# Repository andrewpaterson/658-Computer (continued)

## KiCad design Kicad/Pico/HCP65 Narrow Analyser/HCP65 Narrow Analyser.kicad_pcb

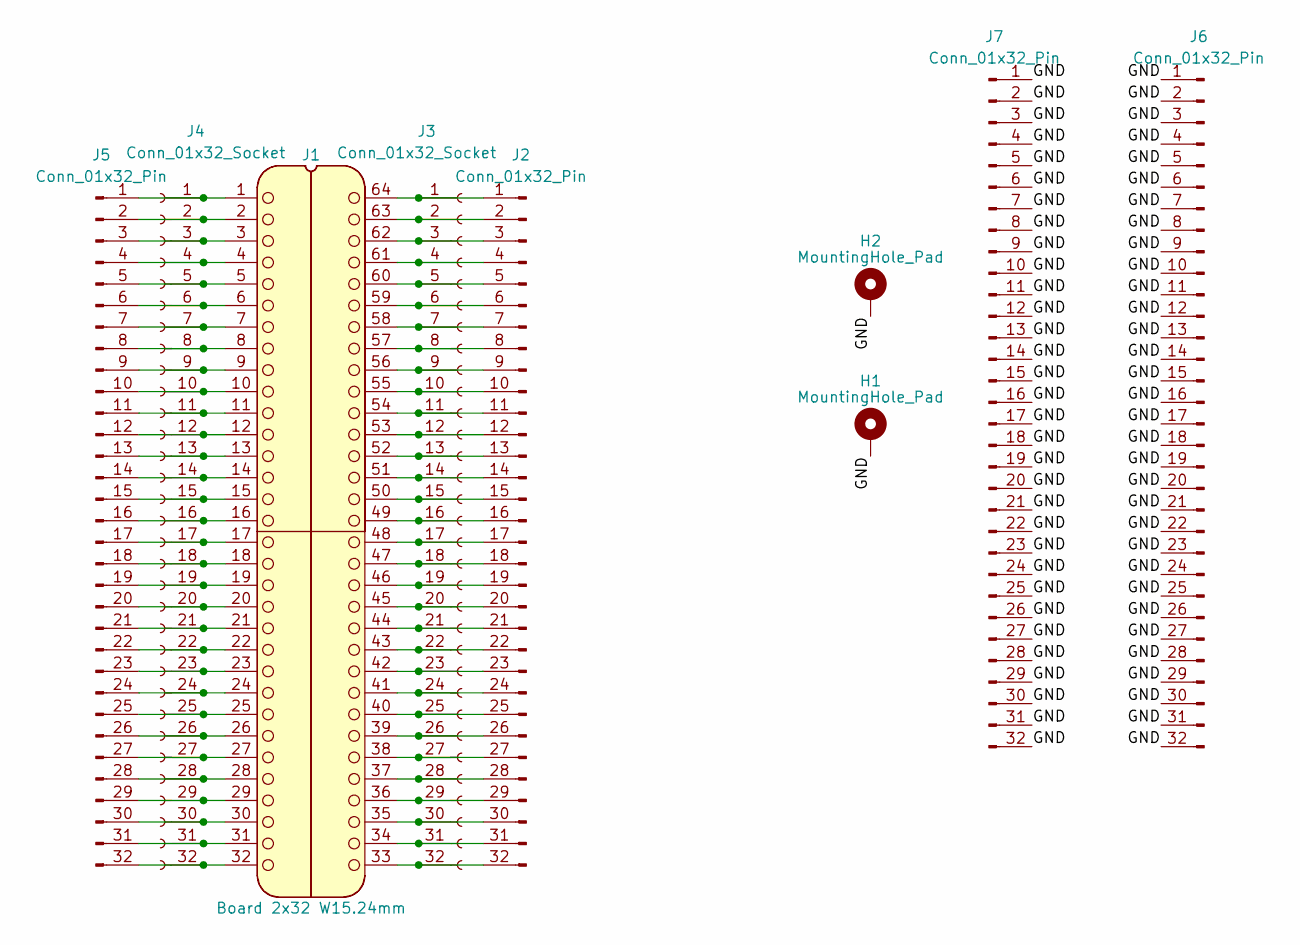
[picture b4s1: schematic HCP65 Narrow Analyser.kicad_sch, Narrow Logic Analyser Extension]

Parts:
H1, H2: MountingHole_Pad; MountingHole_3.2mm_M3_Pad
J1: Board 2x32 W15.24mm; DIP-64_Board_W15.24mm_Nak
J2, J5, J6, J7: Conn_01x32_Pin; PinHeader_1x32_P2.54mm_Vertical
J3, J4: Conn_01x32_Socket; PinSocket_1x32_P2.54mm_Vertical

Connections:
/GND: H1.1, H2.1, J6.1, J6.2, J6.3, J6.4, J6.5, J6.6, J6.7, J6.8, J6.9, J6.10, J6.11, J6.12, J6.13, J6.14, J6.15, J6.16, J6.17, J6.18, J6.19, J6.20, J6.21, J6.22, J6.23, J6.24, J6.25, J6.26, J6.27, J6.28, J6.29, J6.30, J6.31, J6.32, J7.1, J7.2, J7.3, J7.4, J7.5, J7.6, J7.7, J7.8, J7.9, J7.10, J7.11, J7.12, J7.13, J7.14, J7.15, J7.16, J7.17, J7.18, J7.19, J7.20, J7.21, J7.22, J7.23, J7.24, J7.25, J7.26, J7.27, J7.28, J7.29, J7.30, J7.31, J7.32
unnamed: J1.64, J2.1, J3.1
unnamed: J1.63, J2.2, J3.2
unnamed: J1.62, J2.3, J3.3
unnamed: J1.61, J2.4, J3.4
unnamed: J1.60, J2.5, J3.5
unnamed: J1.59, J2.6, J3.6
unnamed: J1.58, J2.7, J3.7
unnamed: J1.57, J2.8, J3.8
unnamed: J1.56, J2.9, J3.9
unnamed: J1.55, J2.10, J3.10
unnamed: J1.54, J2.11, J3.11
unnamed: J1.53, J2.12, J3.12
unnamed: J1.52, J2.13, J3.13
unnamed: J1.51, J2.14, J3.14
unnamed: J1.50, J2.15, J3.15
unnamed: J1.49, J2.16, J3.16
unnamed: J1.48, J2.17, J3.17
unnamed: J1.47, J2.18, J3.18
unnamed: J1.46, J2.19, J3.19
unnamed: J1.45, J2.20, J3.20
unnamed: J1.44, J2.21, J3.21
unnamed: J1.43, J2.22, J3.22
unnamed: J1.42, J2.23, J3.23
unnamed: J1.41, J2.24, J3.24
unnamed: J1.40, J2.25, J3.25
unnamed: J1.39, J2.26, J3.26
unnamed: J1.38, J2.27, J3.27
unnamed: J1.37, J2.28, J3.28
unnamed: J1.36, J2.29, J3.29
unnamed: J1.35, J2.30, J3.30
unnamed: J1.34, J2.31, J3.31
unnamed: J1.33, J2.32, J3.32
unnamed: J1.1, J4.1, J5.1
unnamed: J1.2, J4.2, J5.2
unnamed: J1.3, J4.3, J5.3
unnamed: J1.4, J4.4, J5.4
unnamed: J1.5, J4.5, J5.5
unnamed: J1.6, J4.6, J5.6
unnamed: J1.7, J4.7, J5.7
unnamed: J1.8, J4.8, J5.8
unnamed: J1.9, J4.9, J5.9
unnamed: J1.10, J4.10, J5.10
unnamed: J1.11, J4.11, J5.11
unnamed: J1.12, J4.12, J5.12
unnamed: J1.13, J4.13, J5.13
unnamed: J1.14, J4.14, J5.14
unnamed: J1.15, J4.15, J5.15
unnamed: J1.16, J4.16, J5.16
unnamed: J1.17, J4.17, J5.17
unnamed: J1.18, J4.18, J5.18
unnamed: J1.19, J4.19, J5.19
unnamed: J1.20, J4.20, J5.20
unnamed: J1.21, J4.21, J5.21
unnamed: J1.22, J4.22, J5.22
unnamed: J1.23, J4.23, J5.23
unnamed: J1.24, J4.24, J5.24
unnamed: J1.25, J4.25, J5.25
unnamed: J1.26, J4.26, J5.26
unnamed: J1.27, J4.27, J5.27
unnamed: J1.28, J4.28, J5.28
unnamed: J1.29, J4.29, J5.29
unnamed: J1.30, J4.30, J5.30
unnamed: J1.31, J4.31, J5.31
unnamed: J1.32, J4.32, J5.32

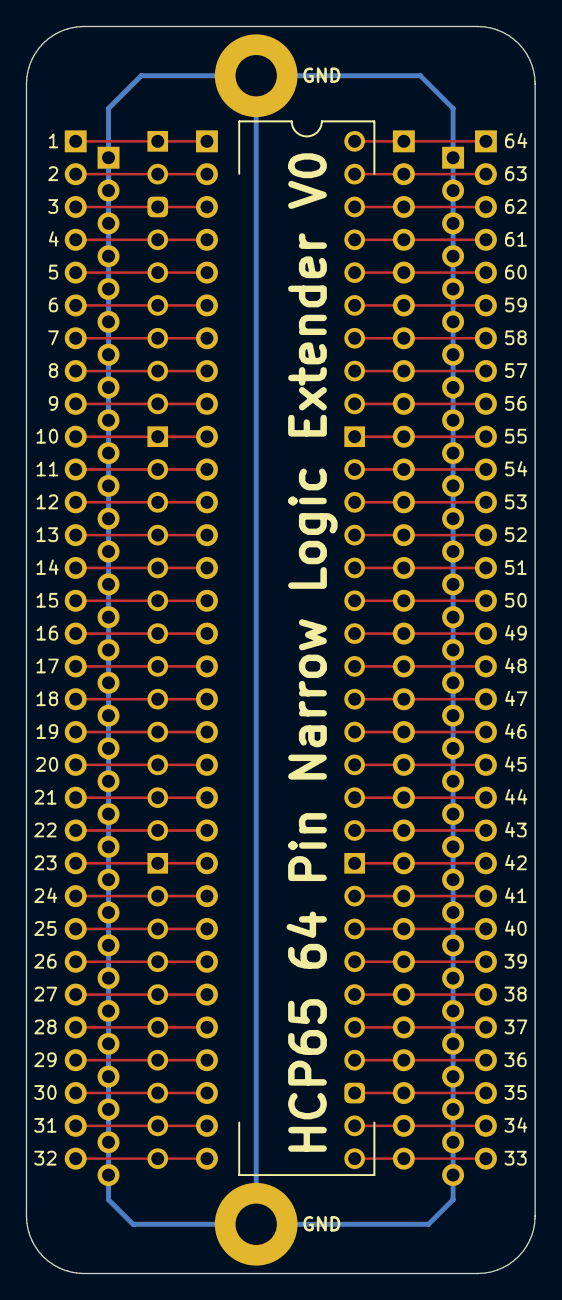
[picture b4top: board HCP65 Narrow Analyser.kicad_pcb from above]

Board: 2 copper layers, 39.4 x 96.5 mm, 9 parts (0 on the bottom side), 65 nets.

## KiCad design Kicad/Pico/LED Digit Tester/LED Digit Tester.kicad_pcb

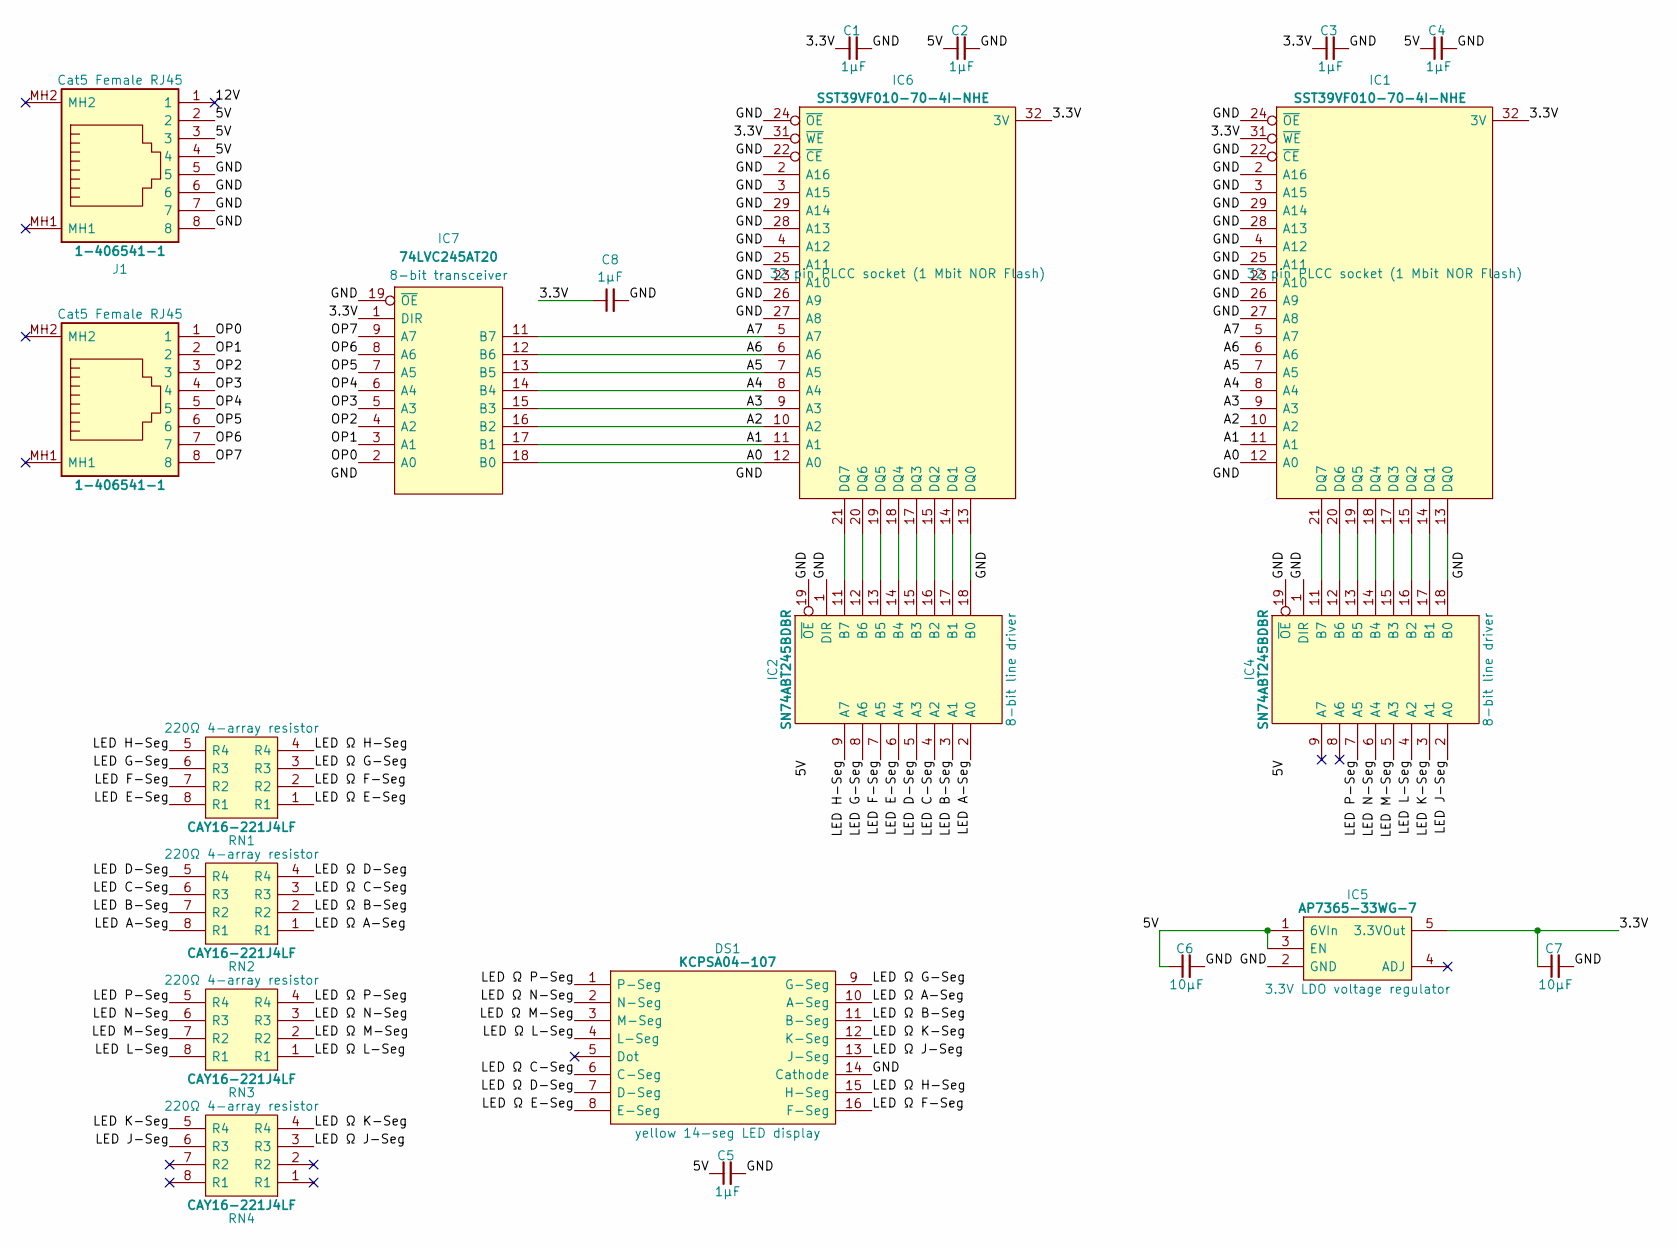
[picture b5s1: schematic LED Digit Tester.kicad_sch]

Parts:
C1, C2, C3, C4, C5, C8: 1μF; C_0805
C6, C7: 10µF; C_0805
DS1: KCPSA04-107; KCPSA04107; Manufacturer_Part_Number KCPSA04-107; Mouser Part Number N/A
IC1, IC6: SST39VF010-70-4I-NHE; 5408803224008; Manufacturer_Part_Number SST39VF010-70-4I-NHE
IC2, IC4: SN74ABT245BDBR; SOP65P780X200-20N; Manufacturer_Part_Number SN74ABT245BDBR; Mouser Part Number 595-SN74ABT245BDBR
IC5: AP7365-33WG-7; SOT95P285X130-5N; Manufacturer_Part_Number AP7365-33WG-7; Mouser Part Number 621-AP7365-33WG-7
IC7: 74LVC245AT20; SOP65P640X120-20N; Manufacturer_Part_Number 74LVC245AT20-13; Mouser Part Number 621-74LVC245AT20-13
J1, J2: 1-406541-1; 1-406541-1_1; Manufacturer_Part_Number 1-406541-1; Mouser Part Number 571-1-406541-1
RN1, RN2, RN3, RN4: CAY16-221J4LF; CAY16-F4; Manufacturer_Part_Number CAY16-221J4LF; Mouser Part Number 652-CAY16-221J4LF

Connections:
/3.3V: C1.1, C3.1, C7.1, C8.1, IC1.31 (~WE), IC1.32 (3V), IC5.5 (3.3VOut), IC6.31 (~WE), IC6.32 (3V), IC7.1 (DIR), IC7.20 (3V)
/5V: C2.1, C4.1, C5.1, C6.1, IC2.20 (5V), IC4.20 (5V), IC5.1 (6VIn), IC5.3 (EN), J1.2, J1.3, J1.4
/12V: J1.1
/A0: IC1.12 (A0), IC6.12 (A0), IC7.18 (B0)
/A1: IC1.11 (A1), IC6.11 (A1), IC7.17 (B1)
/A2: IC1.10 (A2), IC6.10 (A2), IC7.16 (B2)
/A3: IC1.9 (A3), IC6.9 (A3), IC7.15 (B3)
/A4: IC1.8 (A4), IC6.8 (A4), IC7.14 (B4)
/A5: IC1.7 (A5), IC6.7 (A5), IC7.13 (B5)
/A6: IC1.6 (A6), IC6.6 (A6), IC7.12 (B6)
/A7: IC1.5 (A7), IC6.5 (A7), IC7.11 (B7)
/GND: C1.2, C2.2, C3.2, C4.2, C5.2, C6.2, C7.2, C8.2, DS1.14 (Cathode), IC1.2 (A16), IC1.3 (A15), IC1.4 (A12), IC1.16 (GND), IC1.22 (~CE), IC1.23 (A10), IC1.24 (~OE), IC1.25 (A11), IC1.26 (A9), IC1.27 (A8), IC1.28 (A13), IC1.29 (A14), IC2.1 (DIR), IC2.10 (GND), IC2.19 (~OE), IC4.1 (DIR), IC4.10 (GND), IC4.19 (~OE), IC5.2 (GND), IC6.2 (A16), IC6.3 (A15), IC6.4 (A12), IC6.16 (GND), IC6.22 (~CE), IC6.23 (A10), IC6.24 (~OE), IC6.25 (A11), IC6.26 (A9), IC6.27 (A8), IC6.28 (A13), IC6.29 (A14), IC7.10 (GND), IC7.19 (~OE), J1.5, J1.6, J1.7, J1.8
/LED A-Seg: IC2.2 (A0), RN2.8 (R1)
/LED B-Seg: IC2.3 (A1), RN2.7 (R2)
/LED C-Seg: IC2.4 (A2), RN2.6 (R3)
/LED D-Seg: IC2.5 (A3), RN2.5 (R4)
/LED E-Seg: IC2.6 (A4), RN1.8 (R1)
/LED F-Seg: IC2.7 (A5), RN1.7 (R2)
/LED G-Seg: IC2.8 (A6), RN1.6 (R3)
/LED H-Seg: IC2.9 (A7), RN1.5 (R4)
/LED J-Seg: IC4.2 (A0), RN4.6 (R3)
/LED K-Seg: IC4.3 (A1), RN4.5 (R4)
/LED L-Seg: IC4.4 (A2), RN3.8 (R1)
/LED M-Seg: IC4.5 (A3), RN3.7 (R2)
/LED N-Seg: IC4.6 (A4), RN3.6 (R3)
/LED P-Seg: IC4.7 (A5), RN3.5 (R4)
/LED Ω A-Seg: DS1.10 (A-Seg), RN2.1 (R1)
/LED Ω B-Seg: DS1.11 (B-Seg), RN2.2 (R2)
/LED Ω C-Seg: DS1.6 (C-Seg), RN2.3 (R3)
/LED Ω D-Seg: DS1.7 (D-Seg), RN2.4 (R4)
/LED Ω E-Seg: DS1.8 (E-Seg), RN1.1 (R1)
/LED Ω F-Seg: DS1.16 (F-Seg), RN1.2 (R2)
/LED Ω G-Seg: DS1.9 (G-Seg), RN1.3 (R3)
/LED Ω H-Seg: DS1.15 (H-Seg), RN1.4 (R4)
/LED Ω J-Seg: DS1.13 (J-Seg), RN4.3 (R3)
/LED Ω K-Seg: DS1.12 (K-Seg), RN4.4 (R4)
/LED Ω L-Seg: DS1.4 (L-Seg), RN3.1 (R1)
/LED Ω M-Seg: DS1.3 (M-Seg), RN3.2 (R2)
/LED Ω N-Seg: DS1.2 (N-Seg), RN3.3 (R3)
/LED Ω P-Seg: DS1.1 (P-Seg), RN3.4 (R4)
/OP0: IC7.2 (A0), J2.1
/OP1: IC7.3 (A1), J2.2
/OP2: IC7.4 (A2), J2.3
/OP3: IC7.5 (A3), J2.4
/OP4: IC7.6 (A4), J2.5
/OP5: IC7.7 (A5), J2.6
/OP6: IC7.8 (A6), J2.7
/OP7: IC7.9 (A7), J2.8
unnamed: IC1.13 (DQ0), IC4.18 (B0)
unnamed: IC1.14 (DQ1), IC4.17 (B1)
unnamed: IC1.15 (DQ2), IC4.16 (B2)
unnamed: IC1.17 (DQ3), IC4.15 (B3)
unnamed: IC1.18 (DQ4), IC4.14 (B4)
unnamed: IC1.19 (DQ5), IC4.13 (B5)
unnamed: IC1.20 (DQ6), IC4.12 (B6)
unnamed: IC1.21 (DQ7), IC4.11 (B7)
unnamed: IC2.18 (B0), IC6.13 (DQ0)
unnamed: IC2.17 (B1), IC6.14 (DQ1)
unnamed: IC2.16 (B2), IC6.15 (DQ2)
unnamed: IC2.15 (B3), IC6.17 (DQ3)
unnamed: IC2.14 (B4), IC6.18 (DQ4)
unnamed: IC2.13 (B5), IC6.19 (DQ5)
unnamed: IC2.12 (B6), IC6.20 (DQ6)
unnamed: IC2.11 (B7), IC6.21 (DQ7)

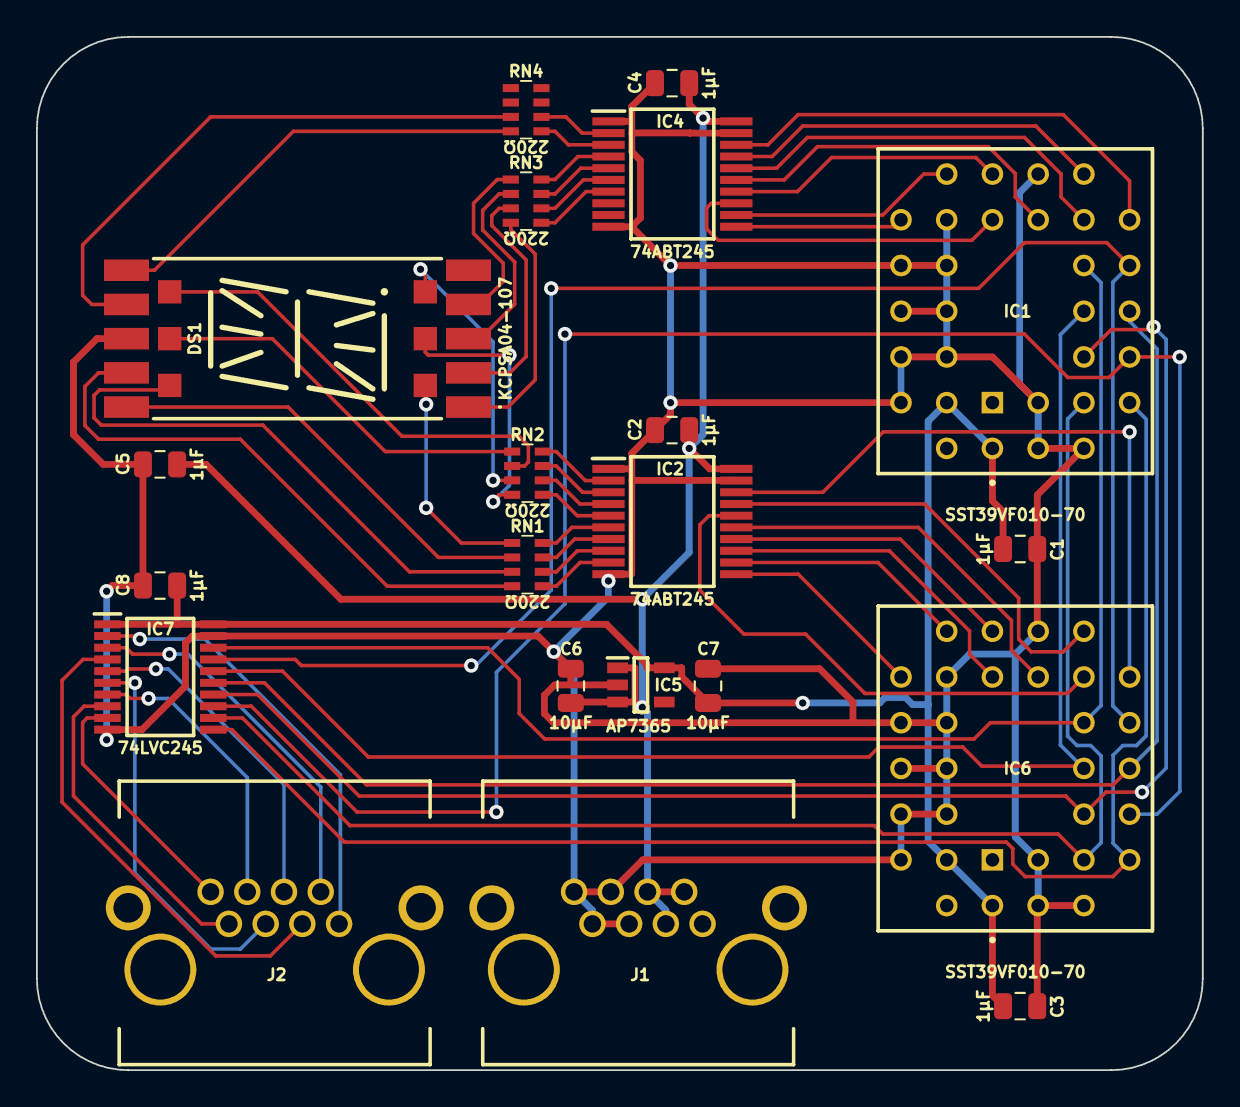
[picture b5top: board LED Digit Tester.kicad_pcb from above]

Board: 2 copper layers, 64.8 x 57.4 mm, 21 parts (0 on the bottom side), 63 nets.

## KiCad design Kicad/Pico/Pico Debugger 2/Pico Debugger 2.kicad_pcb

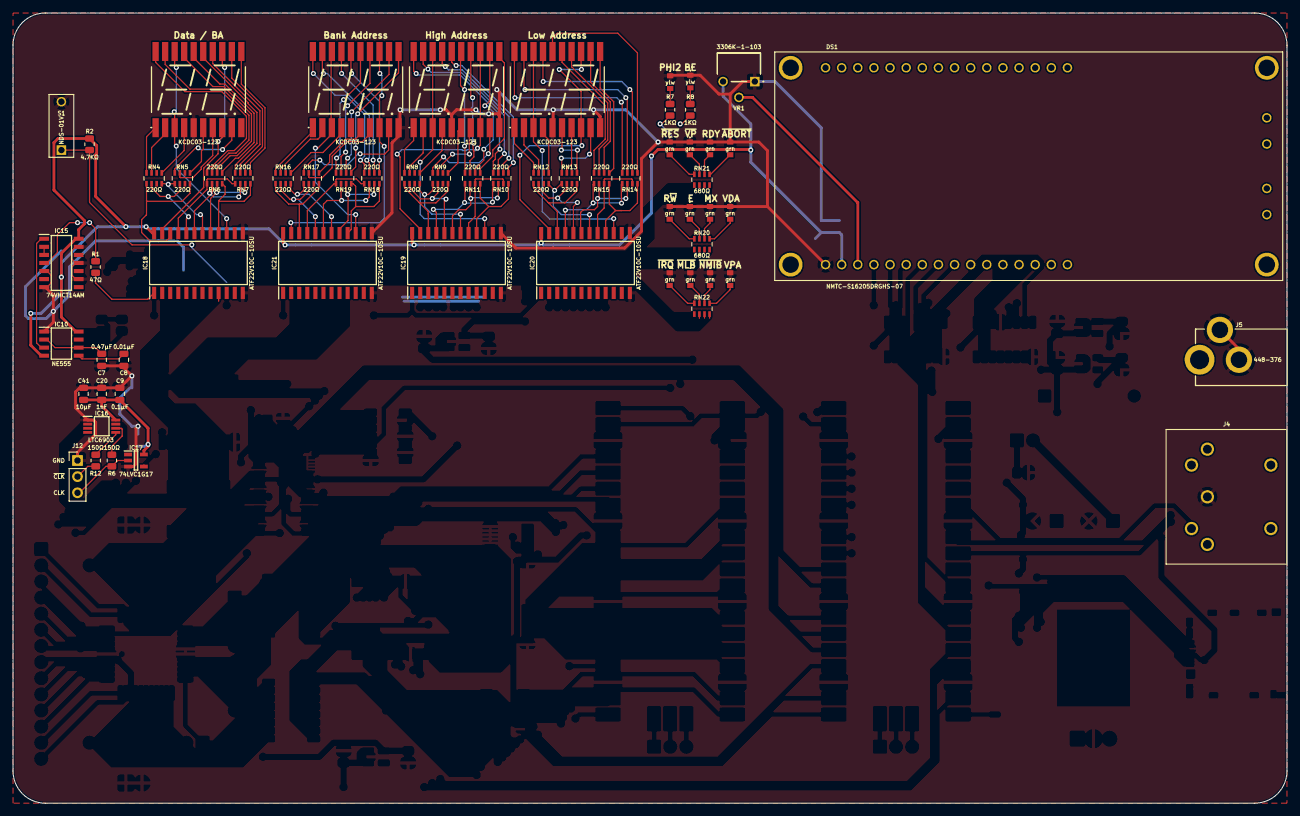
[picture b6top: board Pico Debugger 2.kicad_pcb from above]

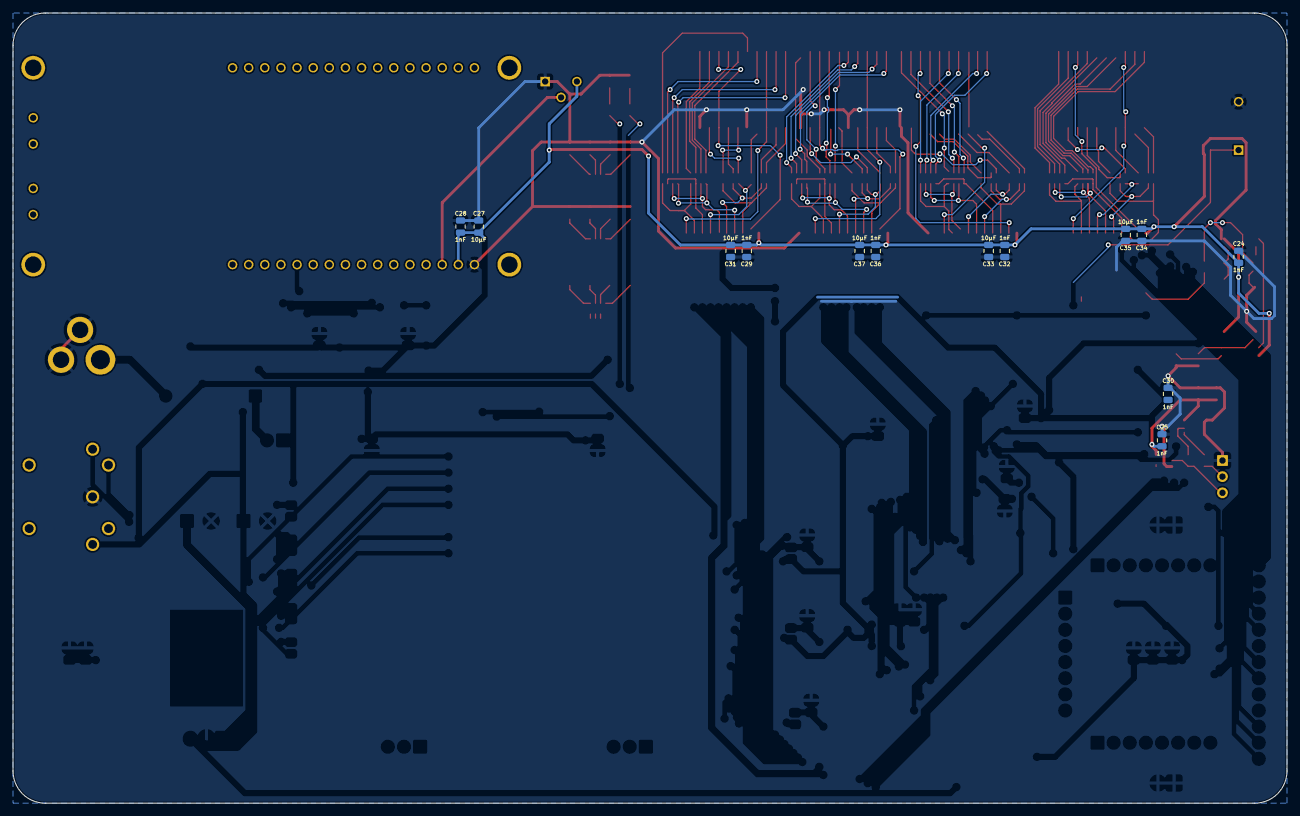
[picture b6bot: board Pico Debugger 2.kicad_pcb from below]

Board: 2 copper layers, 200.7 x 124.5 mm, 75 parts (13 on the bottom side), 123 nets.

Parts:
C7, C8, C9, C20, C24, C25, C27, C28, C29, C30, C31, C32, C33, C34, C35, C36, C37, C41: C_0805
DS1: NMTC-S16205DRGHS-07; NMTCS16205DRGHS07_1
DS2, DS3, DS4, DS5: KCDC03-123; KCDC03123
IC10: NE555DRG4; SOIC127P600X175-8N
IC15: 74VHCT14AM; SOIC127P600X175-14N
IC16: LTC6903CMS8#PBF; SOP65P490X110-8N
IC17: 74LVC1G17GV,125; SOT95P275X110-5N
IC18, IC19, IC20, IC21: ATF22V10C-10SU; SOIC127P1032X265-24N
J4: 491-087; 491087
J5: 448-376; 448376
J12: Conn_01x03_Male; PinHeader_1x03_P2.54mm_Vertical
LED2, LED3: 150224YS73100A; 150224BS73100A
LED4, LED5, LED6, LED7, LED8, LED9, LED10, LED11, LED12, LED13, LED14, LED15: 150224VS73100A
R1, R2, R6, R7, R8, R12: R_0805
RN4, RN5, RN6, RN7, RN8, RN9, RN10, RN11, RN12, RN13, RN14, RN15, RN16, RN17, RN18, RN19: CAY16-221J4LF; CAY1647R0F4LF
RN20, RN21, RN22: CAY16-681J4LF; CAY16-J4
S1: NDS-01V; NDS01V
VR1: 3306K-1-103; 3306K1103

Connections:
/3.3V: C9.1, C20.1, C25.1, C30.1, C41.1, IC16.8 (V+), IC17.5 (3V)
/5V: C24.1, C27.1, C28.1, C29.1, C31.1, C32.1, C33.1, C34.1, C35.1, C36.1, C37.1, DS1.2 (5V), IC10.4 (RESET), IC10.8 (VCC), IC15.14 (5V), IC18.24 (5V), IC19.24 (5V), IC20.24 (5V), IC21.24 (5V), R2.2, VR1.3 (VIN)
/300Hz: IC18.1 (CLK/IN), IC19.1 (CLK/IN), IC20.1 (CLK/IN), IC21.1 (CLK/IN), R1.1
/BE: IC16.7 (OE), R8.1
/Bank Address Display/Digit 0 A Seg: IC21.17 (I/O3), RN18.7 (R2), RN19.7 (R2)
/Bank Address Display/Digit 0 B Seg: IC21.16 (I/O2), RN18.8 (R1), RN19.8 (R1)
/Bank Address Display/Digit 0 C Seg: IC21.18 (I/O4), RN16.4 (R4), RN17.1 (R1)
/Bank Address Display/Digit 0 D Seg: IC21.20 (I/O6), RN16.2 (R2), RN17.2 (R2)
/Bank Address Display/Digit 0 E Seg: IC21.22 (I/O8), RN16.1 (R1), RN17.4 (R4)
/Bank Address Display/Digit 0 F Seg: IC21.19 (I/O5), RN18.6 (R3), RN19.6 (R3)
/Bank Address Display/Digit 0 G Seg: IC21.21 (I/O7), RN18.5 (R4), RN19.5 (R4)
/Bank Address Display/Digit L0 Cathode: DS5.3 (Cathode_{(Left)}), DS5.18 (Cathode_{(Left)}), IC21.15 (I/O1)
/Bank Address Display/Digit R0 Cathode: DS5.8 (Cathode_{(Right)}), DS5.13 (Cathode_{(Right)}), IC21.23 (I/O9)
/Clk: IC16.6 (CLK), R6.1
/Data Display/Digit 0 A Seg: IC18.17 (I/O3), RN6.7 (R2), RN7.7 (R2)
/Data Display/Digit 0 B Seg: IC18.16 (I/O2), RN6.8 (R1), RN7.8 (R1)
/Data Display/Digit 0 C Seg: IC18.18 (I/O4), RN4.4 (R4), RN5.1 (R1)
/Data Display/Digit 0 D Seg: IC18.20 (I/O6), RN4.2 (R2), RN5.2 (R2)
/Data Display/Digit 0 E Seg: IC18.22 (I/O8), RN4.1 (R1), RN5.4 (R4)
/Data Display/Digit 0 F Seg: IC18.19 (I/O5), RN6.6 (R3), RN7.6 (R3)
/Data Display/Digit 0 G Seg: IC18.21 (I/O7), RN6.5 (R4), RN7.5 (R4)
/Data Display/Digit L0 Cathode: DS2.3 (Cathode_{(Left)}), DS2.18 (Cathode_{(Left)}), IC18.15 (I/O1)
/Data Display/Digit R0 Cathode: DS2.8 (Cathode_{(Right)}), DS2.13 (Cathode_{(Right)}), IC18.23 (I/O9)
/GND: C7.2, C8.2, C9.2, C20.2, C24.2, C25.2, C27.2, C28.2, C29.2, C30.2, C31.2, C32.2, C33.2, C34.2, C35.2, C36.2, C37.2, C41.2, DS1.1 (GND), DS2.5 (Dot_{(Left)}), DS2.10 (Dot_{(Right)}), DS3.5 (Dot_{(Left)}), DS3.10 (Dot_{(Right)}), DS4.5 (Dot_{(Left)}), DS4.10 (Dot_{(Right)}), DS5.5 (Dot_{(Left)}), DS5.10 (Dot_{(Right)}), IC10.1 (GND), IC15.5 (3A), IC15.7 (GND), IC15.9 (4A), IC15.11 (5A), IC15.13 (6A), IC16.1 (GND), IC17.3 (GND), IC18.12 (GND), IC18.13 (IN10), IC19.12 (GND), IC19.13 (IN10), IC20.12 (GND), IC20.13 (IN10), IC21.12 (GND), IC21.13 (IN10), J4.2, J5.B1 (GND), J5.C1 (GND), J12.1, LED2.1, LED3.1, LED4.1, LED5.1, LED6.1, LED7.1, LED8.1, LED9.1, LED10.1, LED11.1, LED12.1, LED13.1, LED14.1, LED15.1, S1.2 (NO), VR1.1 (GND)
/High Address Display/Digit 0 A Seg: IC19.17 (I/O3), RN10.7 (R2), RN11.7 (R2)
/High Address Display/Digit 0 B Seg: IC19.16 (I/O2), RN10.8 (R1), RN11.8 (R1)
/High Address Display/Digit 0 C Seg: IC19.18 (I/O4), RN8.4 (R4), RN9.1 (R1)
/High Address Display/Digit 0 D Seg: IC19.20 (I/O6), RN8.2 (R2), RN9.2 (R2)
/High Address Display/Digit 0 E Seg: IC19.22 (I/O8), RN8.1 (R1), RN9.4 (R4)
/High Address Display/Digit 0 F Seg: IC19.19 (I/O5), RN10.6 (R3), RN11.6 (R3)
/High Address Display/Digit 0 G Seg: IC19.21 (I/O7), RN10.5 (R4), RN11.5 (R4)
/High Address Display/Digit L0 Cathode: DS3.3 (Cathode_{(Left)}), DS3.18 (Cathode_{(Left)}), IC19.15 (I/O1)
/High Address Display/Digit R0 Cathode: DS3.8 (Cathode_{(Right)}), DS3.13 (Cathode_{(Right)}), IC19.23 (I/O9)
/Low Address Display/Digit 0 A Seg: IC20.17 (I/O3), RN14.7 (R2), RN15.7 (R2)
/Low Address Display/Digit 0 B Seg: IC20.16 (I/O2), RN14.8 (R1), RN15.8 (R1)
/Low Address Display/Digit 0 C Seg: IC20.18 (I/O4), RN12.4 (R4), RN13.1 (R1)
/Low Address Display/Digit 0 D Seg: IC20.20 (I/O6), RN12.2 (R2), RN13.2 (R2)
/Low Address Display/Digit 0 E Seg: IC20.22 (I/O8), RN12.1 (R1), RN13.4 (R4)
/Low Address Display/Digit 0 F Seg: IC20.19 (I/O5), RN14.6 (R3), RN15.6 (R3)
/Low Address Display/Digit 0 G Seg: IC20.21 (I/O7), RN14.5 (R4), RN15.5 (R4)
/Low Address Display/Digit L0 Cathode: DS4.3 (Cathode_{(Left)}), DS4.18 (Cathode_{(Left)}), IC20.15 (I/O1)
/Low Address Display/Digit R0 Cathode: DS4.8 (Cathode_{(Right)}), DS4.13 (Cathode_{(Right)}), IC20.23 (I/O9)
/PHI2: IC17.4 (Y), R7.1
/Tame Clk: IC17.2 (A), J12.3, R6.2
/V_{0}: DS1.3 (V_{O}), VR1.2 (VOUT)
/~LED Enable: IC18.10 (IN8), IC18.11 (IN9), IC19.10 (IN8), IC19.11 (IN9), IC20.10 (IN8), IC20.11 (IN9), IC21.10 (IN8), IC21.11 (IN9), R2.1, S1.1 (COM)
unnamed: C7.1, IC10.2 (TRIG), IC10.6 (THRES)
unnamed: C8.1, IC10.5 (CONT)
unnamed: DS2.1 (E-Seg_{(Left)}), RN4.8 (R1)
unnamed: DS2.2 (D-Seg_{(Left)}), RN4.7 (R2)
unnamed: DS2.4 (C-Seg_{(Left)}), RN4.5 (R4)
unnamed: DS2.6 (E-Seg_{(Right)}), RN5.5 (R4)
unnamed: DS2.7 (D-Seg_{(Right)}), RN5.7 (R2)
unnamed: DS2.9 (C-Seg_{(Right)}), RN5.8 (R1)
unnamed: DS2.11 (B-Seg_{(Right)}), RN7.1 (R1)
unnamed: DS2.12 (A-Seg_{(Right)}), RN7.2 (R2)
unnamed: DS2.14 (F-Seg_{(Right)}), RN7.3 (R3)
unnamed: DS2.15 (G-Seg_{(Right)}), RN7.4 (R4)
unnamed: DS2.16 (B-Seg_{(Left)}), RN6.1 (R1)
unnamed: DS2.17 (A-Seg_{(Left)}), RN6.2 (R2)
unnamed: DS2.19 (F-Seg_{(Left)}), RN6.3 (R3)
unnamed: DS2.20 (G-Seg_{(Left)}), RN6.4 (R4)
unnamed: DS3.1 (E-Seg_{(Left)}), RN8.8 (R1)
unnamed: DS3.2 (D-Seg_{(Left)}), RN8.7 (R2)
unnamed: DS3.4 (C-Seg_{(Left)}), RN8.5 (R4)
unnamed: DS3.6 (E-Seg_{(Right)}), RN9.5 (R4)
unnamed: DS3.7 (D-Seg_{(Right)}), RN9.7 (R2)
unnamed: DS3.9 (C-Seg_{(Right)}), RN9.8 (R1)
unnamed: DS3.11 (B-Seg_{(Right)}), RN11.1 (R1)
unnamed: DS3.12 (A-Seg_{(Right)}), RN11.2 (R2)
unnamed: DS3.14 (F-Seg_{(Right)}), RN11.3 (R3)
unnamed: DS3.15 (G-Seg_{(Right)}), RN11.4 (R4)
unnamed: DS3.16 (B-Seg_{(Left)}), RN10.1 (R1)
unnamed: DS3.17 (A-Seg_{(Left)}), RN10.2 (R2)
unnamed: DS3.19 (F-Seg_{(Left)}), RN10.3 (R3)
unnamed: DS3.20 (G-Seg_{(Left)}), RN10.4 (R4)
unnamed: DS4.1 (E-Seg_{(Left)}), RN12.8 (R1)
unnamed: DS4.2 (D-Seg_{(Left)}), RN12.7 (R2)
unnamed: DS4.4 (C-Seg_{(Left)}), RN12.5 (R4)
unnamed: DS4.6 (E-Seg_{(Right)}), RN13.5 (R4)
unnamed: DS4.7 (D-Seg_{(Right)}), RN13.7 (R2)
unnamed: DS4.9 (C-Seg_{(Right)}), RN13.8 (R1)
unnamed: DS4.11 (B-Seg_{(Right)}), RN15.1 (R1)
unnamed: DS4.12 (A-Seg_{(Right)}), RN15.2 (R2)
unnamed: DS4.14 (F-Seg_{(Right)}), RN15.3 (R3)
unnamed: DS4.15 (G-Seg_{(Right)}), RN15.4 (R4)
unnamed: DS4.16 (B-Seg_{(Left)}), RN14.1 (R1)
unnamed: DS4.17 (A-Seg_{(Left)}), RN14.2 (R2)
unnamed: DS4.19 (F-Seg_{(Left)}), RN14.3 (R3)
unnamed: DS4.20 (G-Seg_{(Left)}), RN14.4 (R4)
unnamed: DS5.1 (E-Seg_{(Left)}), RN16.8 (R1)
unnamed: DS5.2 (D-Seg_{(Left)}), RN16.7 (R2)
unnamed: DS5.4 (C-Seg_{(Left)}), RN16.5 (R4)
unnamed: DS5.6 (E-Seg_{(Right)}), RN17.5 (R4)
unnamed: DS5.7 (D-Seg_{(Right)}), RN17.7 (R2)
unnamed: DS5.9 (C-Seg_{(Right)}), RN17.8 (R1)
unnamed: DS5.11 (B-Seg_{(Right)}), RN19.1 (R1)
unnamed: DS5.12 (A-Seg_{(Right)}), RN19.2 (R2)
unnamed: DS5.14 (F-Seg_{(Right)}), RN19.3 (R3)
unnamed: DS5.15 (G-Seg_{(Right)}), RN19.4 (R4)
unnamed: DS5.16 (B-Seg_{(Left)}), RN18.1 (R1)
unnamed: DS5.17 (A-Seg_{(Left)}), RN18.2 (R2)
unnamed: DS5.19 (F-Seg_{(Left)}), RN18.3 (R3)
unnamed: DS5.20 (G-Seg_{(Left)}), RN18.4 (R4)
unnamed: IC10.3 (OUT), IC15.1 (1A)
unnamed: IC15.2 (1Y), IC15.3 (2A)
unnamed: IC15.4 (2Y), R1.2
unnamed: IC16.5 (~CLK), R12.1
unnamed: J12.2, R12.2
unnamed: LED2.2, R7.2
unnamed: LED3.2, R8.2
unnamed: LED4.2, RN20.8 (R1)
unnamed: LED5.2, RN20.7 (R2)
unnamed: LED6.2, RN20.6 (R3)
unnamed: LED7.2, RN20.5 (R4)
unnamed: LED8.2, RN21.8 (R1)
unnamed: LED9.2, RN21.7 (R2)
unnamed: LED10.2, RN21.6 (R3)
unnamed: LED11.2, RN21.5 (R4)
unnamed: LED12.2, RN22.8 (R1)
unnamed: LED13.2, RN22.7 (R2)
unnamed: LED14.2, RN22.6 (R3)
unnamed: LED15.2, RN22.5 (R4)
